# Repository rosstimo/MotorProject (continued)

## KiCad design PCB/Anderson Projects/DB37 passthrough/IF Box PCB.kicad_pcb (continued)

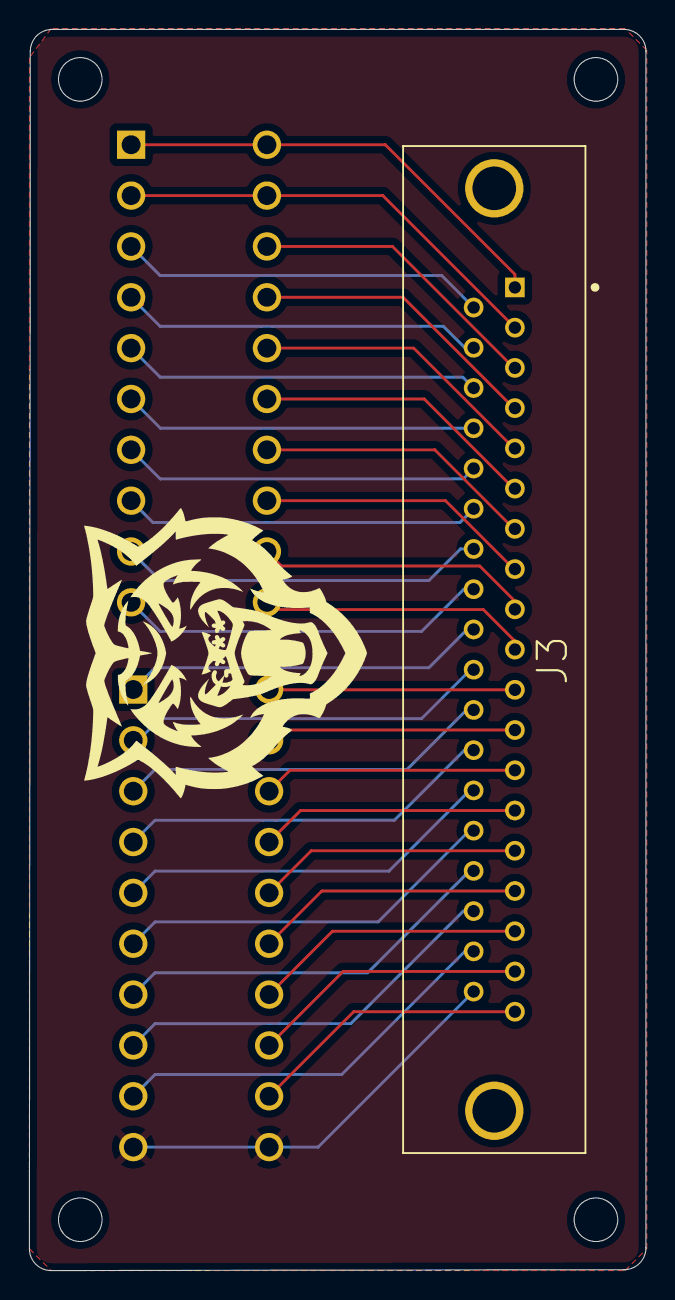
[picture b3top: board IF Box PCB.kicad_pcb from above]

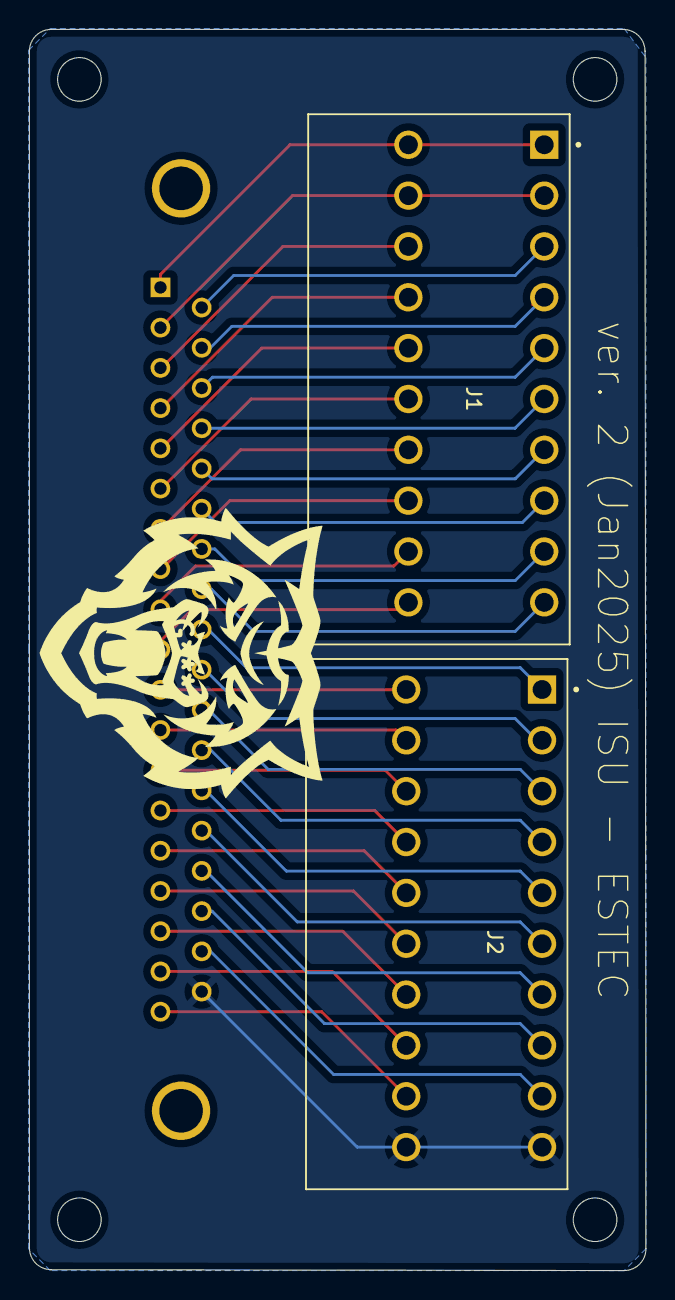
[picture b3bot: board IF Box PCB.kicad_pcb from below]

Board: 2 copper layers, 42.4 x 85.4 mm, 3 parts (2 on the bottom side), 37 nets.

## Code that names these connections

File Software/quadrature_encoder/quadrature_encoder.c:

/**
 * Copyright (c) 2023 Raspberry Pi (Trading) Ltd.
 *
 * SPDX-License-Identifier: BSD-3-Clause
 */

#include <stdio.h>
#include <stdlib.h>
#include "pico/stdlib.h"
#include "hardware/pio.h"
#include "hardware/timer.h"
#include "hardware/pwm.h"


#include "quadrature_encoder.pio.h"

//
// ---- quadrature encoder interface example
//
// the PIO program reads phase A/B of a quadrature encoder and increments or
// decrements an internal counter to keep the current absolute step count
// updated. At any point, the main code can query the current count by using
// the quadrature_encoder_*_count functions. The counter is kept in a full
// 32 bit register that just wraps around. Two's complement arithmetic means
// that it can be interpreted as a 32-bit signed or unsigned value, and it will
// work anyway.
//
// As an example, a two wheel robot being controlled at 100Hz, can use two
// state machines to read the two encoders and in the main control loop it can
// simply ask for the current encoder counts to get the absolute step count. It
// can also subtract the values from the last sample to check how many steps
// each wheel as done since the last sample period.
//
// One advantage of this approach is that it requires zero CPU time to keep the
// encoder count updated and because of that it supports very high step rates.
//

void pwm_pin_init(uint pin){
    uint slice_num = pwm_gpio_to_slice_num(pin);
    
    // Get some sensible defaults for the slice configuration. By default, the
    // counter is allowed to wrap over its maximum range (0 to 2**16-1)
    pwm_config config = pwm_get_default_config();
    // Set divider, reduces counter clock to sysclock/this value
    pwm_config_set_clkdiv(&config, 8.f);
    // Load the configuration into our PWM slice, and set it running.
    pwm_init(slice_num, &config, true);

}

int main() {
    int new_value, delta, old_value = 0;

    // Base pin to connect the A phase of the encoder.
    // The B phase must be connected to the next pin
    const uint PIN_AB = 2;
    const uint PIN_FWD = 16;
    const uint PIN_REV = 17;
    const uint PIN_PWM_POS = 18;
    const uint PIN_PWM_SPD = 19;
    const uint PIN_PWM_POSx10 =20;
    
    // max AB encoder changes per second
    const double speed_max = 4700;
    // max counts = 7 for 775 motor and 240 for gearmotor
    const double position_max = 980;
    
    double speed = 0;
    double position = 0;
    double positionX10 = 0;

    // Configure LED direction pins
    gpio_init(PIN_FWD);
    gpio_set_dir(PIN_FWD, GPIO_OUT);
    gpio_init(PIN_REV);
    gpio_set_dir(PIN_REV, GPIO_OUT);

    // Configure PWM outputs (Position and Velocity)
    gpio_set_function(PIN_PWM_POS, GPIO_FUNC_PWM);
    gpio_set_function(PIN_PWM_SPD, GPIO_FUNC_PWM);
    gpio_set_function(PIN_PWM_POSx10, GPIO_FUNC_PWM);

    // Initiallize the PWM slice with appropriate config
    pwm_pin_init(PIN_PWM_POS);
    // Initialize the PWM slice for the x10 Position
    pwm_pin_init(PIN_PWM_POSx10);

    // If you need serial
    stdio_init_all();

    // Configure the PIO program
    PIO pio = pio0;
    const uint sm = 0;

    // we don't really need to keep the offset, as this program must be loaded
    // at offset 0
    pio_add_program(pio, &quadrature_encoder_program);
    quadrature_encoder_program_init(pio, sm, PIN_AB, 0);

    while (1) {
        // note: thanks to two's complement arithmetic delta will always
        // be correct even when new_value wraps around MAXINT / MININT
        new_value = quadrature_encoder_get_count(pio, sm);
        delta = new_value - old_value;
        old_value = new_value;

	// speed in counts/second 
	speed = abs((double)delta)/0.1f;
	
	position += delta;
	if (position > position_max){
	    position -= position_max;
	}else if (position < 0){
	    position = position_max + position;
	}
	
	// positionX10 used to check calibration over 10 revs
	positionX10 += delta;
	if (positionX10 > position_max * 10){
	    positionX10 -= (position_max * 10);
	}else if (positionX10 < 0){
	    positionX10 = (position_max * 10) + positionX10;
	}
	
	pwm_set_gpio_level(PIN_PWM_SPD, speed *65535.f/speed_max);
	pwm_set_gpio_level(PIN_PWM_POS, position *65535.f/position_max);
	pwm_set_gpio_level(PIN_PWM_POSx10, positionX10 *65535.f/(position_max * 10));
	
	if(delta > 0){
	    gpio_put(PIN_FWD, 1);
	    gpio_put(PIN_REV, 0);
	}else if (delta < 0){
	    gpio_put(PIN_FWD, 0);
	    gpio_put(PIN_REV, 1);
	}else {
	    gpio_put(PIN_FWD, 0);
	    gpio_put(PIN_REV, 0);
	}

	// Serial is on GP0 and GP1 by default
        printf("position %8d, delta %6d\n", new_value, delta);
        sleep_ms(100);
    }
}

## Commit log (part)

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2024-04-30 Motor Drawing, Overview, and Specifications
2024-05-03 SVG Files for Motor Mount
2024-05-03 wheel for RPM measurements
2024-05-06 19mm center hole, 15mm length
2024-05-06 TS25GA370H Motor Mount for Testing
2024-05-06 updated body1
2024-05-08 add dirs
2024-05-08 add license
2024-05-08 add contribution guidlines
2024-05-09 migrate Hbridge
2024-05-10 add TTL Motor Encoder Schem
2024-05-10 Initial CircuitPython code for testing Encoder
2024-05-12 update schema
2024-05-12 ignore auto save, lock files
2024-05-12 update 7476 symbol
2024-05-12 split schema into sheets
2024-05-13 moved SVG files to Mechanical
2024-05-13 Motor Specifications and Initial Test Data
2024-05-14 testing git merger
2024-05-14 Testing git
2024-05-14 Testing Push/Pull
2024-05-14 fax all problems
2024-05-19 Updated Software README and added the Pico C code folder
2024-05-21 Create **Needs added** TS-25GA370H-20 specs
    Details to be added to the motor spec section
2024-05-21 Update **Needs added** TS-25GA370H-20 specs
    Added some comments to TimL
2024-05-21 Create **Needs added** Pico encoder documentation
2024-05-22 Update **Needs added** Pico encoder documentation
2024-05-22 H_Bridge Schematic
2024-05-22 Rename **Needs added** Pico encoder documentation to --Needs added-- Pico encoder documentation
    Invalid file name
2024-05-22 Rename **Needs added** TS-25GA370H-20 specs to --Needs added-- TS-25GA370H-20 specs
    Fixed file name
2024-05-22 added .md file extension'
2024-05-23 cleanup and rename
2024-05-23 update schema notes
2024-05-23 update symbols, add decouple
2024-05-23 update pdf plot
2024-05-23 Added Pico Documentation and updated TS Specs
2024-05-23 HBridgeGerberFiles
2024-05-23 Pico Encoder Documentation and TS specifications update and compiled single document H-Bridge Motor Control Circuit
2024-05-25 added DB37 to Terminals PCB gerber zip
2024-05-29 Motor Coupler Drawing
2024-05-29 MotorCoupler 3MF file
2024-05-29 added holes
2024-06-06 add tested analog speed circuit
2024-06-06 git ignore
2024-06-06 plot
2024-06-18 start pico PCB
2024-06-19 schema nearly finished
2024-06-24 clean up PICO schema
2024-07-01 TL494 Gerber Files
2024-07-01 Layout complete, need silkscreen and BOM
2024-07-01 Delete PCB/MotorInterfacePiPico/MotorInterfacePiPico.pdf
    delete old schema
2024-07-01 New Version of DB37 Terminal adapter PCB
2024-07-03 PCB layout complete, need to DNC, need BOM
2024-07-03 Layout complete, need BOM
2024-07-03 add gerbers, need BOM
2024-07-24 Stop Light and Traffic Intersection 3MF
2025-02-06 renamed DB37 to Terminals v0.zip Added DB37 to Terminals v2.zip Parts list from DigiKey order
2025-05-12 Added DB37 passthrough project folder
2025-05-12 don't ignore BOM.csv
2025-05-12 old BOM
2025-05-13 BOM with digikey links for order
2025-05-14 Rev2 PCB TL494 with Hbridge
2025-05-14 V2 Schematic
2025-05-27 R9, R12, R14, R15 updated to 10K
2025-05-29 CarTrackPCB
2025-05-29 update pcb
2025-05-30 Surface Mount Board design
2025-05-31 Added .DS_Store to .gitignore
2025-06-02 Made new Anderson PCB project and reverted Tim R's folder
2025-06-02 cleanup Pico_H-bridge_complete project folder prior to edits
2025-06-02 Anderson Schematic with opto-couples prior to change to zener diodes
2025-06-04 remove submodule
2025-06-04 Changed Dig inputs to zener buffers, removed all opto-couples, rebuilt h-bridge logic.
2025-06-04 allow any file named BOM.csv
2025-06-04 add MotorInterfaceDiscretekeybinds
2025-06-04 add MotorInterfacePiPico
2025-06-04 shootout init
2025-06-05 Anderson PCB ready for board layout
2025-06-05 main schem start
2025-06-05 fix power
2025-06-06 working on h-bridge logic
2025-06-06 fix h-bridge pwm logic
2025-06-06 change MOSFET/LED drivers to MOSFET to keep ttl in spec
2025-06-06 ready for cleanup and layout
2025-06-07 working on part source
2025-06-07 commit before schema change
2025-06-07 new h-bridge config
2025-06-07 ready for footprints
2025-06-08 most footprints, added and measured/confirmed
2025-06-08 all footprints
2025-06-08 fix trim pot footprint
2025-06-09 Anderson Pico_H-bridge_complete Gerbers ready to order
2025-06-17 continue four layer layout
2025-06-21 minor edits prior to ordering, and assembly document creation
2025-06-23 Updated Anderson Schematic to fix V0 issues
2025-07-01 Final Board version prior to testing motor with pulleys. This version would not turn the motor when connected to a generator. The Vgs values for Mosfets needed increased to 10v. Other improvements to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
2025-07-01 (R's still mostly 0603)H-bridge circuit updated to achieve 10v Vgs. Replaced S0/S1 logic with Fwd/Rev simplified logic. Added header footprint for testing alternative capacitors. Minimized test point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
2025-07-10 Gerber files for Pico_H-bridge_complete v1 generated
2025-07-14 house keeping
2025-07-14 housekeeping
2025-07-14 GerbFileStopLight
2025-07-14 StopLight3dPrintFiles
2025-07-14 StopLight 3D Print Files
2025-07-14 db37Bracket
2025-07-30 Anderson Motor Interface Board v2 complete and ordered.
2025-11-21 Anderson Motor Interface Board v3. - Bengal eyes LED for both directions - heatsink pads on back of board - DIN rail mount Added Heater Box Schematic files in Documentation
